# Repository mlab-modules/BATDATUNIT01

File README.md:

# BATDATUNIT01 - Power and Data Storage Module

The BATDATUNIT01 is power and data storage module incorporating an ATmea1284p microcontroller paired with a five 18650 Li-ion safely rechargable accumulator cells. It is a reliable power source for extended durations, making it an integral component in various detectors or measuring systems.

## Features

- **Microcontroller**: [ATmega1284p](https://www.microchip.com/wwwproducts/en/ATmega1284p) provides robust processing capabilities to manage complex tasks efficiently.
- **Battery Pack**: A Set of up to five Li-ion batteries offers substantial power, facilitating long-term operations without frequent recharging.
- **USB-C Charging**: Enables hassle-free charging with a USB-C interface, ensuring the module is readily powered for sustained use.
- **Charging and Monitoring Circuits**: The [BQ25628E](https://www.ti.com/product/BQ25628) circuit oversees the charging, while the [BQ34Z100](https://www.ti.com/product/BQ34Z100) gauge monitors the battery state for optimal energy management.

## Applications

The BATDATUNIT01 is designed for versatility:

- As a **power module for semiconductor particle detectors** like the [AIRDOS04](https://github.com/UniversalScientificTechnologies/AIRDOS04), it ensures uninterrupted data acquisition in environmental monitoring.
- It can be integrated into **remote sensing stations**, providing consistent power and data logging capabilities for long-term ecological studies.
- In **automated weather stations**, the module's resilience and sensor suite offers valuable insights into meteorological conditions.
- The module can be deployed in **mobile robotics** for energy supply and environmental data collection, aiding navigation and decision-making processes.
- It is also ideal for **educational purposes**, as a hands-on tool to teach about energy management, data acquisition, and sensor integration.

The robust design and connectivity options make the BATDATUNIT01 a dependable choice for powering and managing data across many scientific applications.

For more detailed information on interfacing and protocols, please refer to the [ATmea1284p datasheet](https://ww1.microchip.com/downloads/en/DeviceDoc/doc8059.pdf) and the communication standards for [UART](https://en.wikipedia.org/wiki/Universal_asynchronous_receiver-transmitter), [I2C](https://www.i2c-bus.org/), [SPI](https://en.wikipedia.org/wiki/Serial_Peripheral_Interface), and [GPIO](https://en.wikipedia.org/wiki/General-purpose_input/output).

## Design

Designed for convenience, the module allows for fast detachment from the measuring part without tools, streamlining the replacement process. Data can be downloaded during battery charging thanks to onboard memory.

## Schematics

### Internal structure

```mermaid

    flowchart TD

    subgraph a[User interfaceI]
        USB[[USB-C\nData + power]]
        UI1([User interface \n Button + battery indicator])
        UI2([User interface \n Button + 3x LED])
    
    end

    USB --USB --> USW

    FTDI -- I2C --> I2CSW
    FTDI -- UART <--> MCU
    MCU -- I2C --> I2CSW[I2C mux]
    MCU[Microcontroller]
    MCU --SPI <--> SDW
    MCU --> SDW

    subgraph one[Memory interface]
    SDR[SD card] <--> SDI
    SDI[SD card interface] -- USB <--> USW
    USW[USB-SWITCH]
    SDW[SD card \n SPI-SWITCH] <--> SDI
    end

    subgraph three[Digital part ]
    USW -- USB <--> FTDI[FTDI\nI2C + UART]

    I2CSW --I2C--> HYG[Hygrometer]
    I2CSW --I2C--> ALT[Pressure sensor]

    I2CSW -- I2C --> I2Cen

    end

    I2CSW --I2C--> GAUGE
    I2CSW --I2C--> charger

    GAUGE --> UI1
    MCU --> UI2

    GAUGE --> PWR3v3
    GAUGE --> PWR3v3E
    GAUGE --> PWR5vE
    
    USB -- Power --> charger

    subgraph two[POWER sources]
    PWR3v3[Power supply\nfor internal 3.3V]
    PWR3v3E[Power supply\nfor detector 3.3V]
    PWR5vE[Power supply\nfor detector 5V]
    
    charger --> GAUGE[Accumulators gauge]
    GAUGE <==> LIION[(5x Li-ion cells)]
    end
    PWR3v3 --> MCU

    PWR3v3E --> DI
    PWR5vE --> DI

    I2Cen[I2C switch] -- I2C --> DI
    DI[[Detector interface]] == GPIO, SPI <==> MCU

```

## Connectivity

A durable Molex connector brings together data and detection with impressive mechanical resilience. It hosts UART, I2C, SPI buses, and extra GPIO signals, providing extensive interfacing options with various systems. The complementary module to the interface connector is [BATDATSOCKET01](https://github.com/mlab-modules/BATDATSOCKET01).

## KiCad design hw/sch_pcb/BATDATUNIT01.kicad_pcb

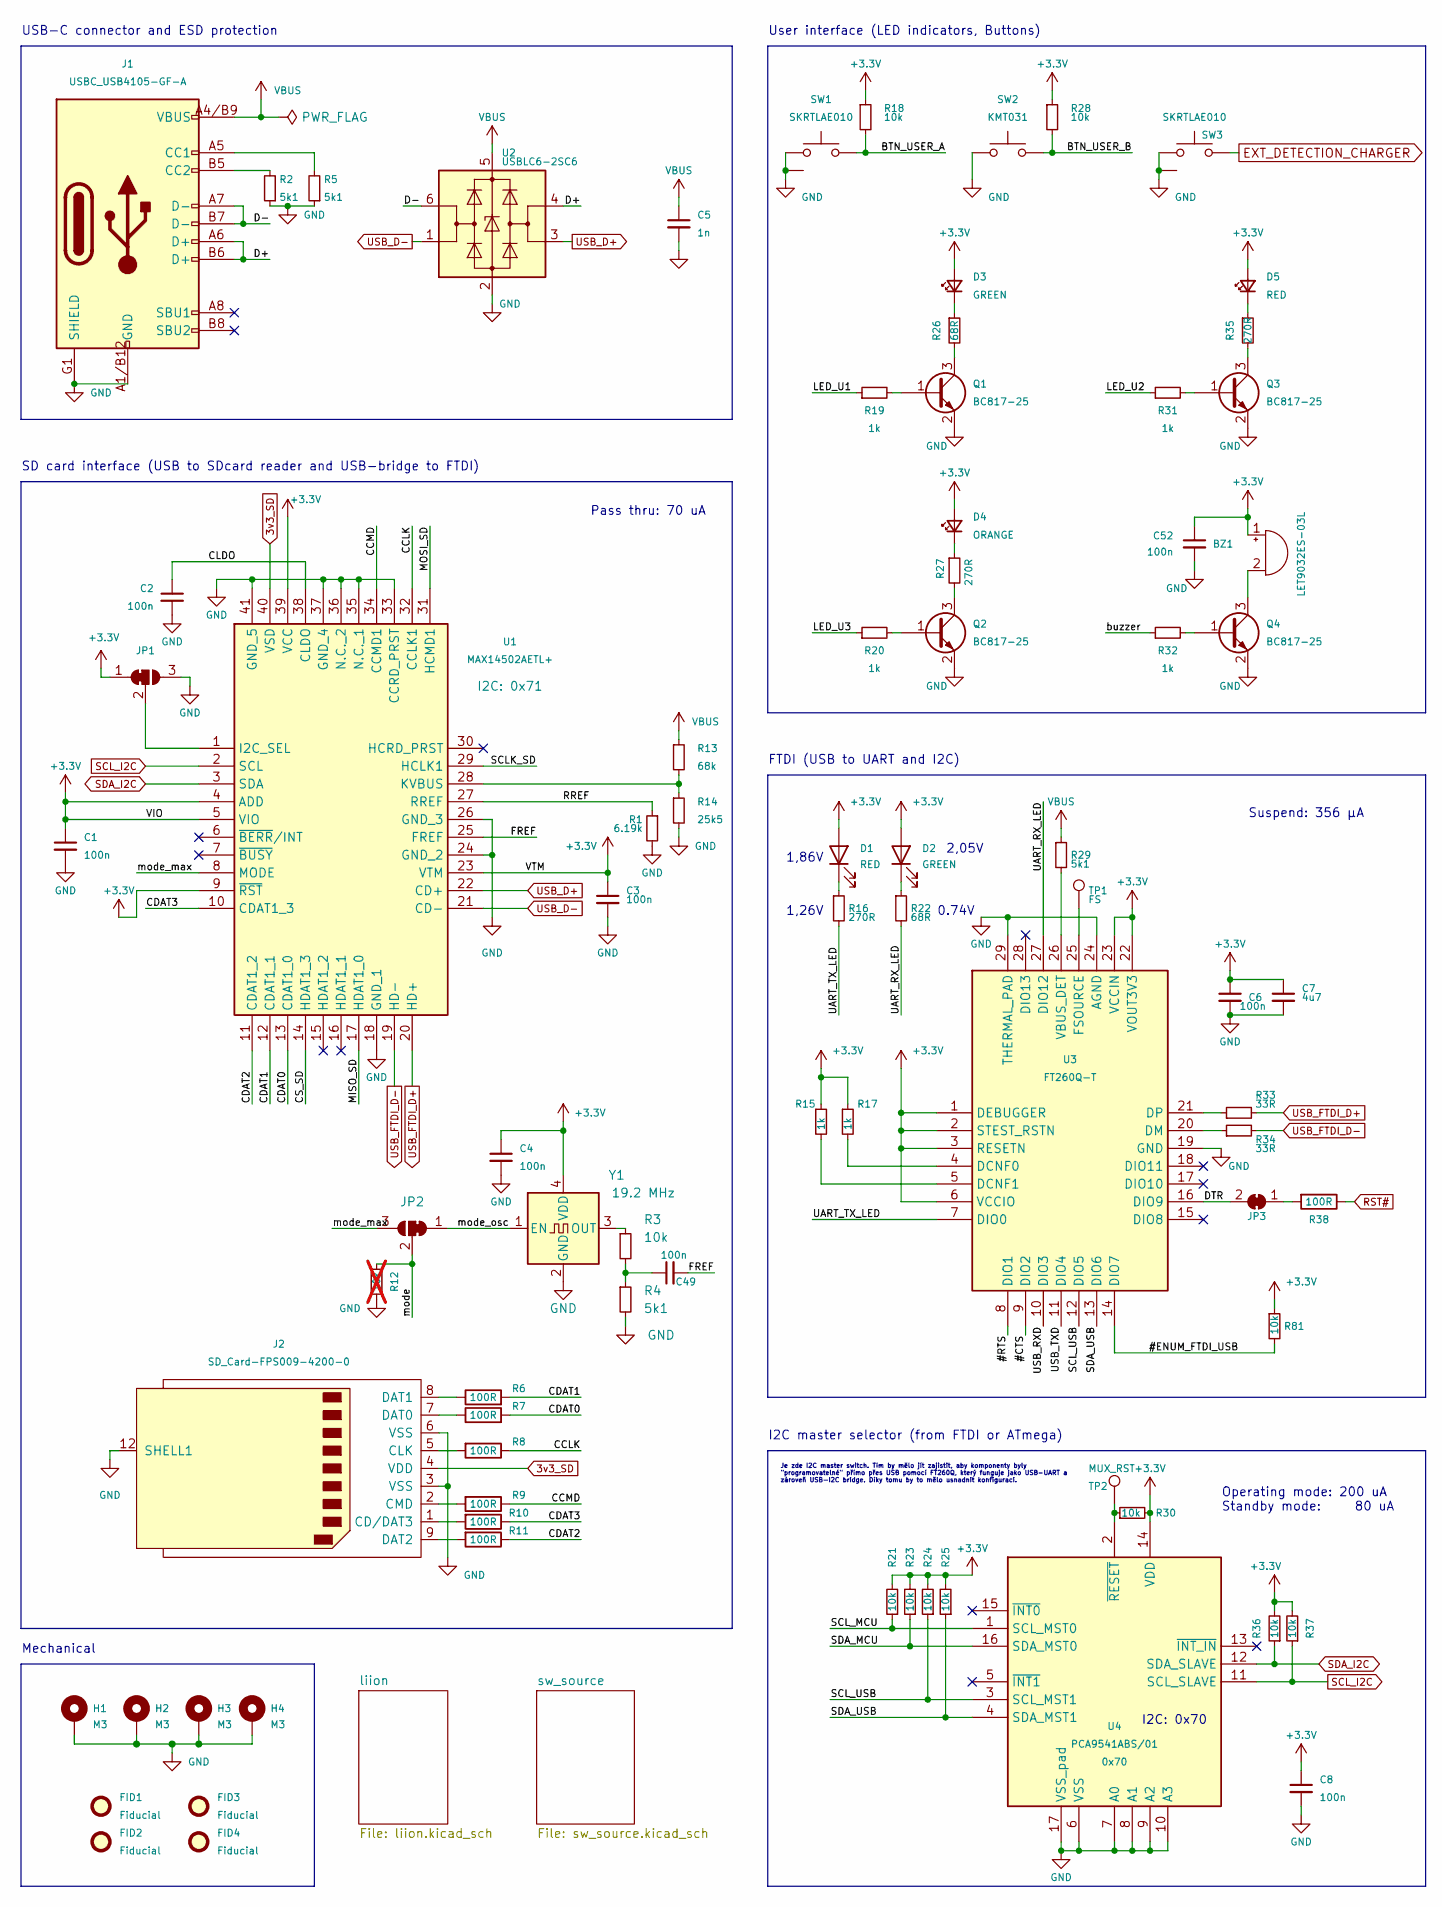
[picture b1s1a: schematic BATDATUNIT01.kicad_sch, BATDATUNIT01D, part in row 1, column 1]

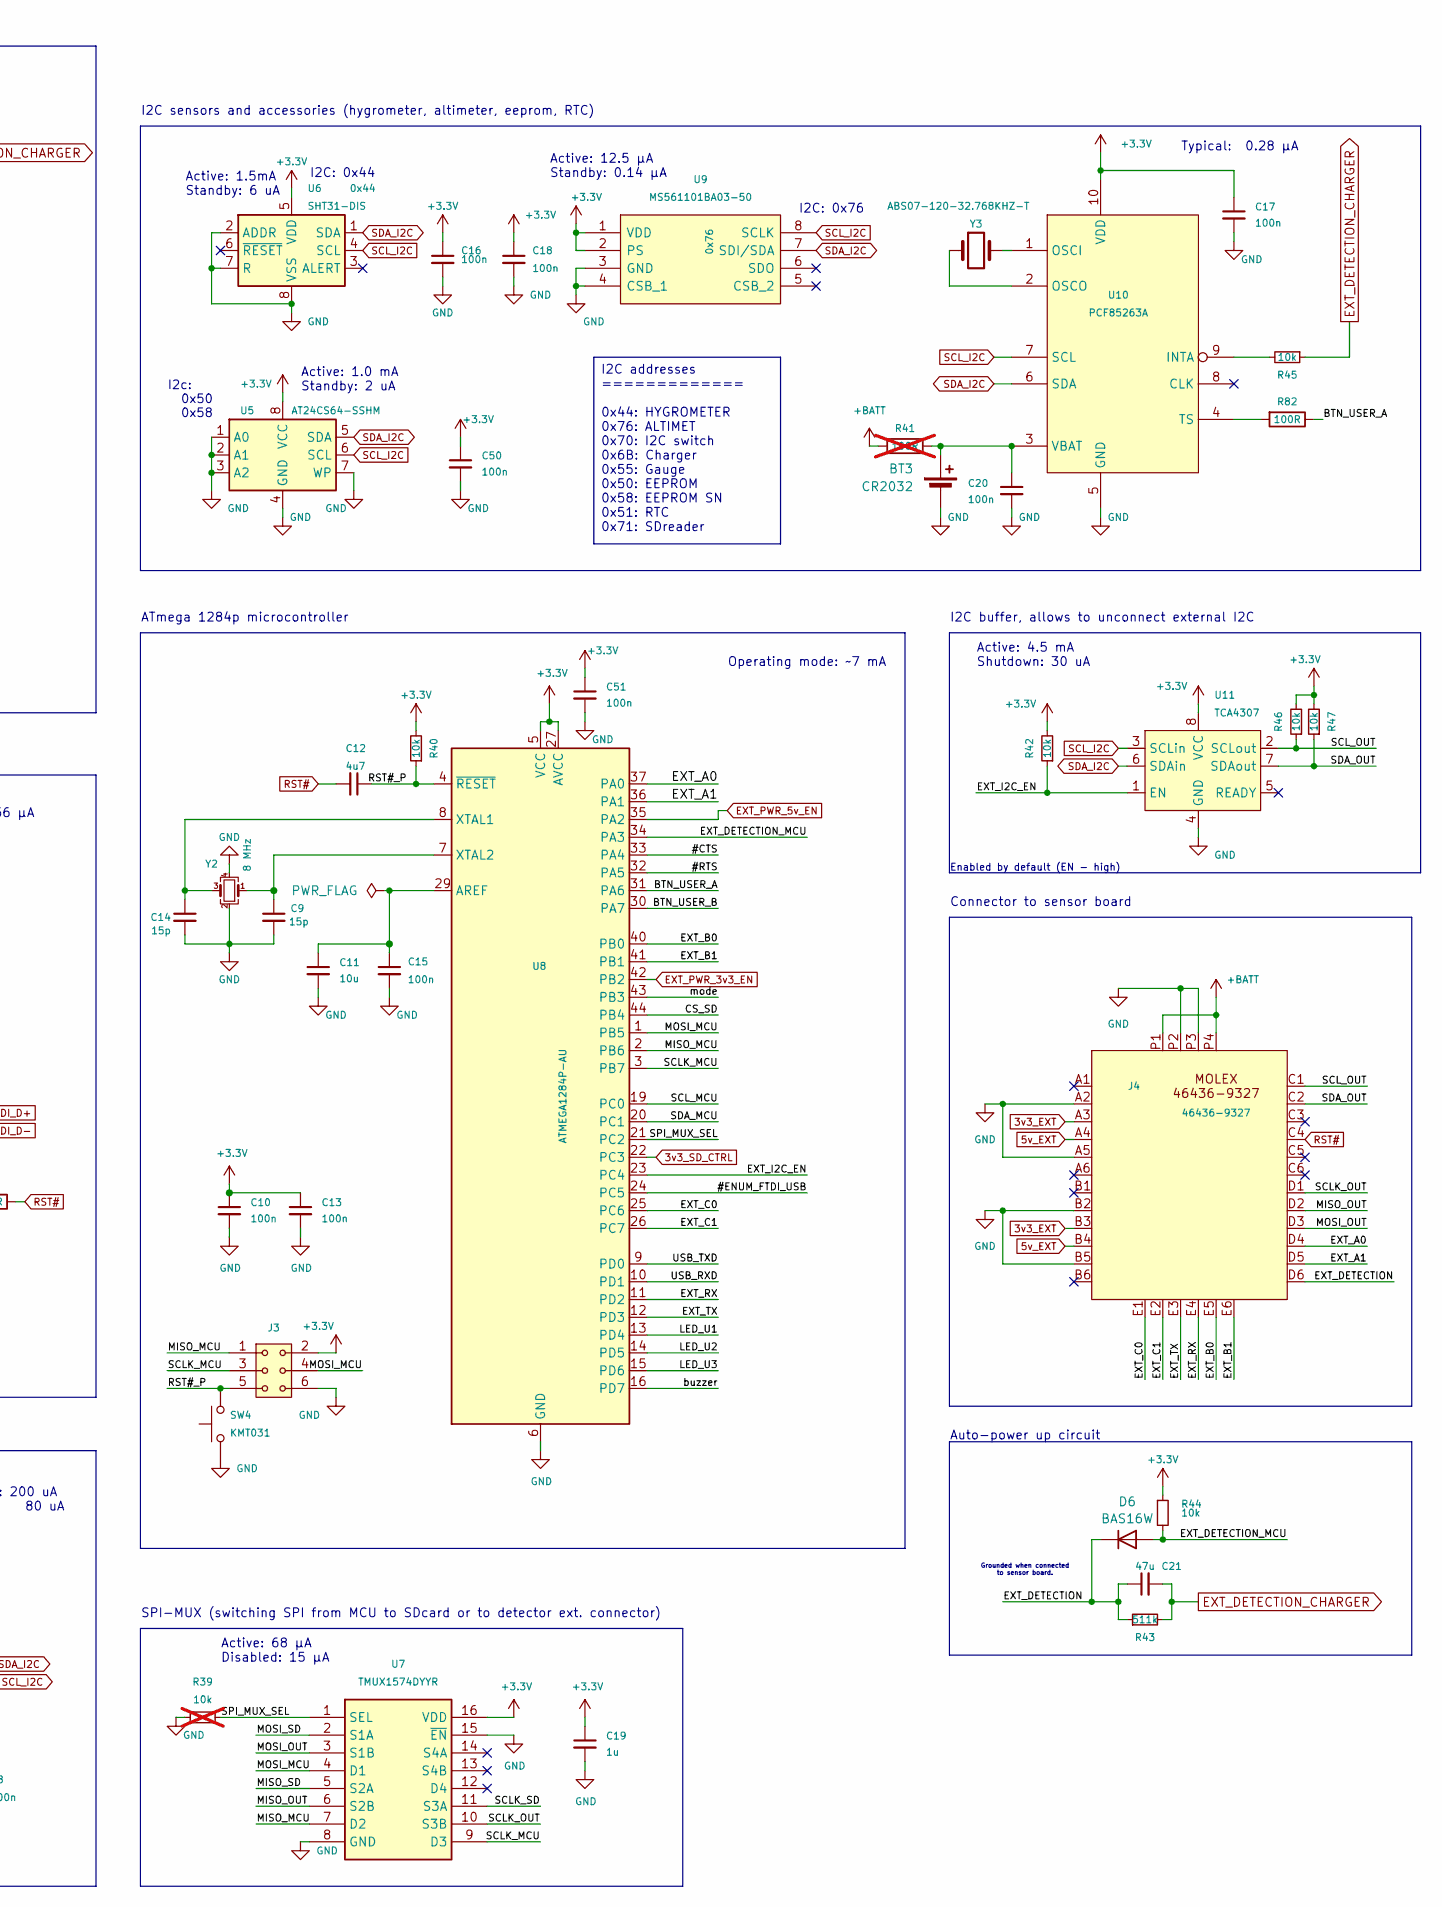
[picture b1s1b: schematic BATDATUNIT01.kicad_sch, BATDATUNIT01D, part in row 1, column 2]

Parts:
BT3: CR2032; BatteryHolder_Keystone_1060_1x2032
BZ1: LET9032ES-03L; MagneticBuzzer_LET9032ES-03L-2.7-16-R
C1, C2, C3, C4, C6, C8, C10, C13, C15, C16, C17, C18, C20, C49, C50, C51, C52: 100n; C_0805_2012Metric
C5: 1n; C_0805_2012Metric; MPN C0805 1u
C7, C12: 4u7; C_0805_2012Metric
C9, C14: 15p; C_0805_2012Metric
C11: 10u; C_0805_2012Metric
C19: 1u; C_0805_2012Metric
C21: 47u; C_0805_2012Metric
D1, D5: RED; SMD_LED_RIGHT_KINGBRIGHT_1605
D2, D3: GREEN; SMD_LED_RIGHT_KINGBRIGHT_1605
D4: ORANGE; SMD_LED_RIGHT_KINGBRIGHT_1605
D6: BAS16W; SOT-323_SC-70
FID1, FID2, FID3, FID4: Fiducial; Fiducial_1mm_Mask2mm
H1, H2, H3, H4: M3; MountingHole_3mm
J1: USBC_USB4105-GF-A; USBC GCT_USB4105-GF-A; MPN USB4105-GF-A
J2: SD_Card-FPS009-4200-0; FPS009-4200-0
J3: HEADER_2x03; SMD_2x03
J4: 46436-9327; MOLEX_46436-9327
JP1: Jumper_3_Bridged12; SolderJumper-3_P1.3mm_Bridged2Bar12_RoundedPad1.0x1.5mm
JP2: SolderJumper_3_Bridged123; SolderJumper-3_P1.3mm_Bridged12_RoundedPad1.0x1.5mm
JP3: SolderJumper_2_Open; SolderJumper-2_P1.3mm_Bridged_RoundedPad1.0x1.5mm
Q1, Q2, Q3, Q4: BC817-25; SOT-23-3
R1: 6.19k; R_0805_2012Metric
R2, R4, R5, R29: 5k1; R_0805_2012Metric
R3, R18, R21, R23, R24, R25, R28, R30, R36, R37, R40, R42, R44, R45, R46, R47, R81: 10k; R_0805_2012Metric
R6, R7, R8, R9, R10, R11, R38, R82: 100R; R_0805_2012Metric
R12, R39: 10k; R_0805_2012Metric; not fitted
R13: 68k; R_0805_2012Metric
R14: 25k5; R_0805_2012Metric
R15, R17, R19, R20, R31, R32: 1k; R_0805_2012Metric
R16, R27, R35: 270R; R_0805_2012Metric
R22, R26: 68R; R_0805_2012Metric
R33, R34: 33R; R_0805_2012Metric
R41: 100R; R_0805_2012Metric; not fitted
R43: 511k; R_0805_2012Metric
SW1, SW3: SKRTLAE010; SKRT
SW2, SW4: KMT031; KMT031 NGJ LHS C&K
TP1: FS; TestPoint_Pad_D1.0mm
TP2: MUX_RST; TestPoint_Pad_D1.5mm
U1: MAX14502AETL+; QFN40P500X500X80-41N; Manufacturer_Part_Number MAX14502AETL+
U2: USBLC6-2SC6; SOT-23-6; LCSC C7519
U3: FT260Q-T; QFN-28-1EP_5x5mm_P0.5mm_EP3.35x3.35mm; Manufacturer_Part_Number FT260Q-T; Mouser Part Number 895-FT260Q-T
U4: PCA9541ABS/01; QFN-16-1EP_4x4mm_P0.65mm_EP2.15x2.15mm; Manufacturer_Part_Number PCA9541ABS/03,118; Mouser Part Number 771-PCA9541ABS03,118
U5: AT24CS64-SSHM; SOIC-8_3.9x4.9mm_P1.27mm
U6: SHT31-DIS; Sensirion_DFN-8-1EP_2.5x2.5mm_P0.5mm_EP1.1x1.7mm
U7: TMUX1574DYYR; SOT-23-16 THIN; Manufacturer_Part_Number TMUX1574DYYR; Mouser Part Number 595-TMUX1574DYYR
U8: ATMEGA1284P-AU; TQFP-44_10x10mm_P0.8mm
U9: MS561101BA03-50; LGA-8_3x5mm_P1.25mm; Mouser Part Number 824-MS561101BA03-50
U10: PCF85263A; TSSOP-10_3x3mm_P0.5mm
U11: TCA4307; VSSOP-8_3.0x3.0mm_P0.65mm
Y1: 19.2 MHz; Crystal_SMD_2520-4Pin_2.5x2.0mm
Y2: 8 MHz; Crystal_SMD_3225-4Pin_3.2x2.5mm
Y3: ABS07-120-32.768KHZ-T; ABS07

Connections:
3v3_EXT: J4.A3, J4.B3; also elsewhere on the board
3v3_SD: J2.4 (VDD), U1.40 (VSD); also elsewhere on the board
3v3_SD_CTRL: U8.22 (PC3); also elsewhere on the board
5v_EXT: J4.A4, J4.B4; also elsewhere on the board
+3.3V: BZ1.1 (-), C1.1, C3.1, C4.1, C6.1, C7.1, C8.1, C10.1, C13.1, C16.1, C17.1, C18.1, C19.1, C50.1, C51.1, C52.1, D1.2 (A), D2.2 (A), D3.2 (A), D4.2 (A), D5.2 (A), J3.2, JP1.1 (A), R15.1, R17.1, R18.1, R21.2, R23.2, R24.2, R25.2, R28.1, R30.2, R36.2, R37.2, R40.2, R42.2, R44.1, R46.2, R47.2, R81.1, U1.4 (ADD), U1.5 (VIO), U1.9 (~RST), U1.23 (VTM), U1.39 (VCC), U3.1 (DEBUGGER), U3.2 (STEST_RSTN), U3.3 (RESETN), U3.6 (VCCIO), U3.22 (VOUT3V3), U3.23 (VCCIN), U4.14 (VDD), U5.8 (VCC), U6.5 (VDD), U7.16 (VDD), U8.5 (VCC), U8.17 (VCC), U8.27 (AVCC), U8.38 (VCC), U9.1 (VDD), U9.2 (PS), U10.10 (VDD), U11.8 (VCC), Y1.4 (VDD); also elsewhere on the board
+BATT: J4.P1, J4.P4, R41.2; also elsewhere on the board
/#CTS: U3.9 (DIO2), U8.33 (PA4)
/#ENUM_FTDI_USB: R81.2, U3.14 (DIO7), U8.24 (PC5)
/#RTS: U3.8 (DIO1), U8.32 (PA5)
/BTN_USER_A: R18.2, R82.1, SW1.1, U8.31 (PA6)
/BTN_USER_B: R28.2, SW2.1, U8.30 (PA7)
/CCLK: R8.1, U1.32 (CCLK1)
/CCMD: R9.1, U1.34 (CCMD1)
/CDAT0: R7.2, U1.13 (CDAT1_0)
/CDAT1: R6.2, U1.12 (CDAT1_1)
/CDAT2: R11.1, U1.11 (CDAT1_2)
/CDAT3: R10.1, U1.10 (CDAT1_3)
/CLDO: C2.1, U1.38 (CLDO)
/CS_SD: U1.14 (HDAT1_3), U8.44 (PB4)
/D+: J1.A6 (D+), J1.B6 (D+), U2.4 (I/O2)
/D-: J1.A7 (D-), J1.B7 (D-), U2.6 (I/O1)
/DTR: JP3.2 (B), U3.16 (DIO9)
/EXT_A0: J4.D4, U8.37 (PA0)
/EXT_A1: J4.D5, U8.36 (PA1)
/EXT_B0: J4.E5, U8.40 (PB0)
/EXT_B1: J4.E6, U8.41 (PB1)
/EXT_C0: J4.E1, U8.25 (PC6)
/EXT_C1: J4.E2, U8.26 (PC7)
/EXT_DETECTION: C21.1, D6.3 (K), J4.D6, R43.1
/EXT_DETECTION_MCU: D6.1 (A), R44.2, U8.34 (PA3)
/EXT_I2C_EN: R42.1, U8.23 (PC4), U11.1 (EN)
/EXT_RX: J4.E4, U8.11 (PD2)
/EXT_TX: J4.E3, U8.12 (PD3)
/FREF: C49.2, U1.25 (FREF)
/LED_U1: R19.1, U8.13 (PD4)
/LED_U2: R31.1, U8.14 (PD5)
/LED_U3: R20.1, U8.15 (PD6)
/MISO_MCU: J3.1, U7.7 (D2), U8.2 (PB6)
/MISO_OUT: J4.D2, U7.6 (S2B)
/MISO_SD: U1.17 (HDAT1_0), U7.5 (S2A)
/MOSI_MCU: J3.4, U7.4 (D1), U8.1 (PB5)
/MOSI_OUT: J4.D3, U7.3 (S1B)
/MOSI_SD: U1.31 (HCMD1), U7.2 (S1A)
/RREF: R1.1, U1.27 (RREF)
/RST#_P: C12.1, J3.5, R40.1, SW4.2, U8.4 (~RESET)
/SCLK_MCU: J3.3, U7.9 (D3), U8.3 (PB7)
/SCLK_OUT: J4.D1, U7.10 (S3B)
/SCLK_SD: U1.29 (HCLK1), U7.11 (S3A)
/SCL_MCU: R21.1, U4.1 (SCL_MST0), U8.19 (PC0)
/SCL_OUT: J4.C1, R46.1, U11.2 (SCLout)
/SCL_USB: R24.1, U3.12 (DIO5), U4.3 (SCL_MST1)
/SDA_MCU: R23.1, U4.16 (SDA_MST0), U8.20 (PC1)
/SDA_OUT: J4.C2, R47.1, U11.7 (SDAout)
/SDA_USB: R25.1, U3.13 (DIO6), U4.4 (SDA_MST1)
/SPI_MUX_SEL: R39.2, U7.1 (SEL), U8.21 (PC2)
/UART_RX_LED: R22.2, U3.27 (DIO12)
/UART_TX_LED: R16.2, U3.7 (DIO0)
/USB_RXD: U3.10 (DIO3), U8.10 (PD1)
/USB_TXD: U3.11 (DIO4), U8.9 (PD0)
/buzzer: R32.1, U8.16 (PD7)
/mode: JP2.2 (C), R12.2, U8.43 (PB3)
/mode_max: JP2.3 (B), U1.8 (MODE)
/mode_osc: JP2.1 (A), Y1.1 (EN)
EXT_DETECTION_CHARGER: C21.2, R43.2, R45.1, SW3.1; also elsewhere on the board
EXT_PWR_3v3_EN: U8.42 (PB2); also elsewhere on the board
EXT_PWR_5v_EN: U8.35 (PA2); also elsewhere on the board
GND: BT3.2 (-), C1.2, C2.2, C3.2, C4.2, C5.2, C6.2, C7.2, C8.2, C9.2, C10.2, C11.2, C13.2, C14.2, C15.2, C16.2, C17.2, C18.2, C19.2, C20.2, C50.2, C51.2, C52.2, H1.1 (1_1), H2.1 (1_1), H3.1 (1_1), H4.1 (1_1), J1.A1/B12 (GND), J1.B1/A12 (GND), J1.G1 (SHIELD), J1.G2 (SHIELD), J1.G3 (SHIELD), J1.G4 (SHIELD), J2.3 (VSS), J2.6 (VSS), J2.12 (SHELL1), J3.6, J4.A2, J4.A5, J4.B2, J4.B5, J4.P2, J4.P3, JP1.3 (B), Q1.2 (E), Q2.2 (E), Q3.2 (E), Q4.2 (E), R1.2, R2.1, R4.2, R5.1, R12.1, R14.2, R39.1, SW1.2, SW1.GND (SHIELD), SW2.2, SW3.2, SW3.GND (SHIELD), SW4.1, U1.18 (GND_1), U1.24 (GND_2), U1.26 (GND_3), U1.33 (CCRD_PRST), U1.35 (N.C._1), U1.36 (N.C._2), U1.37 (GND_4), U1.41 (GND_5), U2.2 (GND), U3.19 (GND), U3.24 (AGND), U3.29 (THERMAL_PAD), U4.6 (VSS), U4.7 (A0), U4.8 (A1), U4.9 (A2), U4.10 (A3), U4.17 (VSS_pad), U5.1 (A0), U5.2 (A1), U5.3 (A2), U5.4 (GND), U5.7 (WP), U6.2 (ADDR), U6.7 (R), U6.8 (VSS), U6.9 (VSS), U7.8 (GND), U7.15 (~EN), U8.6 (GND), U8.18 (GND), U8.28 (GND), U8.39 (GND), U9.3 (GND), U9.4 (CSB_1), U10.5 (GND), U11.4 (GND), Y1.2 (GND), Y2.2, Y2.4; also elsewhere on the board
unnamed: BT3.1 (+), C20.1, R41.1, U10.3 (VBAT)
unnamed: BZ1.2 (+), Q4.3 (C)
unnamed: C49.1, R3.2, R4.1
unnamed: D1.1 (K), R16.1
unnamed: D2.1 (K), R22.1
unnamed: D3.1 (K), R26.1
unnamed: D4.1 (K), R27.1
unnamed: D5.1 (K), R35.1
unnamed: J1.A5 (CC1), R5.2
unnamed: J1.B5 (CC2), R2.2
unnamed: J2.1 (CD/DAT3), R10.2
unnamed: J2.5 (CLK), R8.2
unnamed: J2.2 (CMD), R9.2
unnamed: J2.7 (DAT0), R7.1
unnamed: J2.8 (DAT1), R6.1
unnamed: J2.9 (DAT2), R11.2
unnamed: JP1.2 (C), U1.1 (I2C_SEL)
unnamed: JP3.1 (A), R38.2
unnamed: Q1.1 (B), R19.2
unnamed: Q1.3 (C), R26.2
unnamed: Q2.1 (B), R20.2
unnamed: Q2.3 (C), R27.2
unnamed: Q3.1 (B), R31.2
unnamed: Q3.3 (C), R35.2
unnamed: Q4.1 (B), R32.2
unnamed: R13.2, R14.1, U1.28 (KVBUS)
unnamed: R17.2, U3.4 (DCNF0)
unnamed: R15.2, U3.5 (DCNF1)
unnamed: R34.1, U3.20 (DM)
unnamed: R33.1, U3.21 (DP)
unnamed: TP1.1 (1_1), U3.25 (FSOURCE)
unnamed: R29.2, U3.26 (VBUS_DET)
unnamed: R30.1, TP2.1 (1_1), U4.2 (~RESET)
unnamed: C11.1, C15.1, U8.29 (AREF)
unnamed: C14.1, U8.8 (XTAL1), Y2.3
unnamed: C9.1, U8.7 (XTAL2), Y2.1
unnamed: R45.2, U10.9 (INTA)
unnamed: U10.1 (OSCI), Y3.2
unnamed: U10.2 (OSCO), Y3.1
unnamed: R82.2, U10.4 (TS)
unnamed: R3.1, Y1.3 (OUT)
RST#: C12.2, J4.C4, R38.1
SCL_I2C: R37.1, U1.2 (SCL), U4.11 (SCL_SLAVE), U5.6 (SCL), U6.4 (SCL), U9.8 (SCLK), U10.7 (SCL), U11.3 (SCLin); also elsewhere on the board
SDA_I2C: R36.1, U1.3 (SDA), U4.12 (SDA_SLAVE), U5.5 (SDA), U6.1 (SDA), U9.7 (SDI/SDA), U10.6 (SDA), U11.6 (SDAin); also elsewhere on the board
USB_D+: U1.22 (CD+), U2.3 (I/O2)
USB_D-: U1.21 (CD-), U2.1 (I/O1)
USB_FTDI_D+: R33.2, U1.20 (HD+)
USB_FTDI_D-: R34.2, U1.19 (HD-)
VBUS: C5.1, J1.A4/B9 (VBUS), J1.B4/A9 (VBUS), R13.1, R29.1, U2.5 (VBUS); also elsewhere on the board

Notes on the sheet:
SPI-MUX (switching SPI from MCU to SDcard or to detector ext. connector)
Active: 4.5 mA Shutdown: 30 uA
Active: 1.5mA Standby: 6 uA
0.74V
Active: 1.0 mA Standby: 2 uA
Suspend: 356 μA
FTDI (USB to UART and I2C)
I2C: 0x44
Active: 12.5 μA Standby: 0.14 μA
Mechanical
I2C buffer, allows to unconnect external I2C
ATmega 1284p microcontroller
1,86V
Pass thru: 70 uA
USB-C connector and ESD protection
Typical: 0.28 μA
I2C sensors and accessories (hygrometer, altimeter, eeprom, RTC)
I2C master selector (from FTDI or ATmega)
User interface (LED indicators, Buttons)
Operating mode: ~7 mA
Auto-power up circuit
Active: 68 μA Disabled: 15 μA
Grounded when connected to sensor board.
2,05V
Connector to sensor board
I2c: 0x50 0x58
I2C: 0x76
Enabled by default (EN - high)
I2C: 0x70
1,26V
Operating mode: 200 uA Standby mode: 80 uA
SD card interface (USB to SDcard reader and USB-bridge to FTDI)
I2C addresses ============= 0x44: HYGROMETER 0x76: ALTIMET 0x70: I2C switch 0x6B: Charger 0x55: Gauge 0x50: EEPROM 0x58: EEPROM SN 0x51: RTC 0x71: SDreader
Je zde I2C master switch. Tím by mělo jít zajistit, aby komponenty byly "programovatelné" přímo přes USB pomocí FT260Q, který funguje jako USB-UART a zároveň USB-I2C bridge. Díky tomu by to mělo usnadnit konfiguraci.

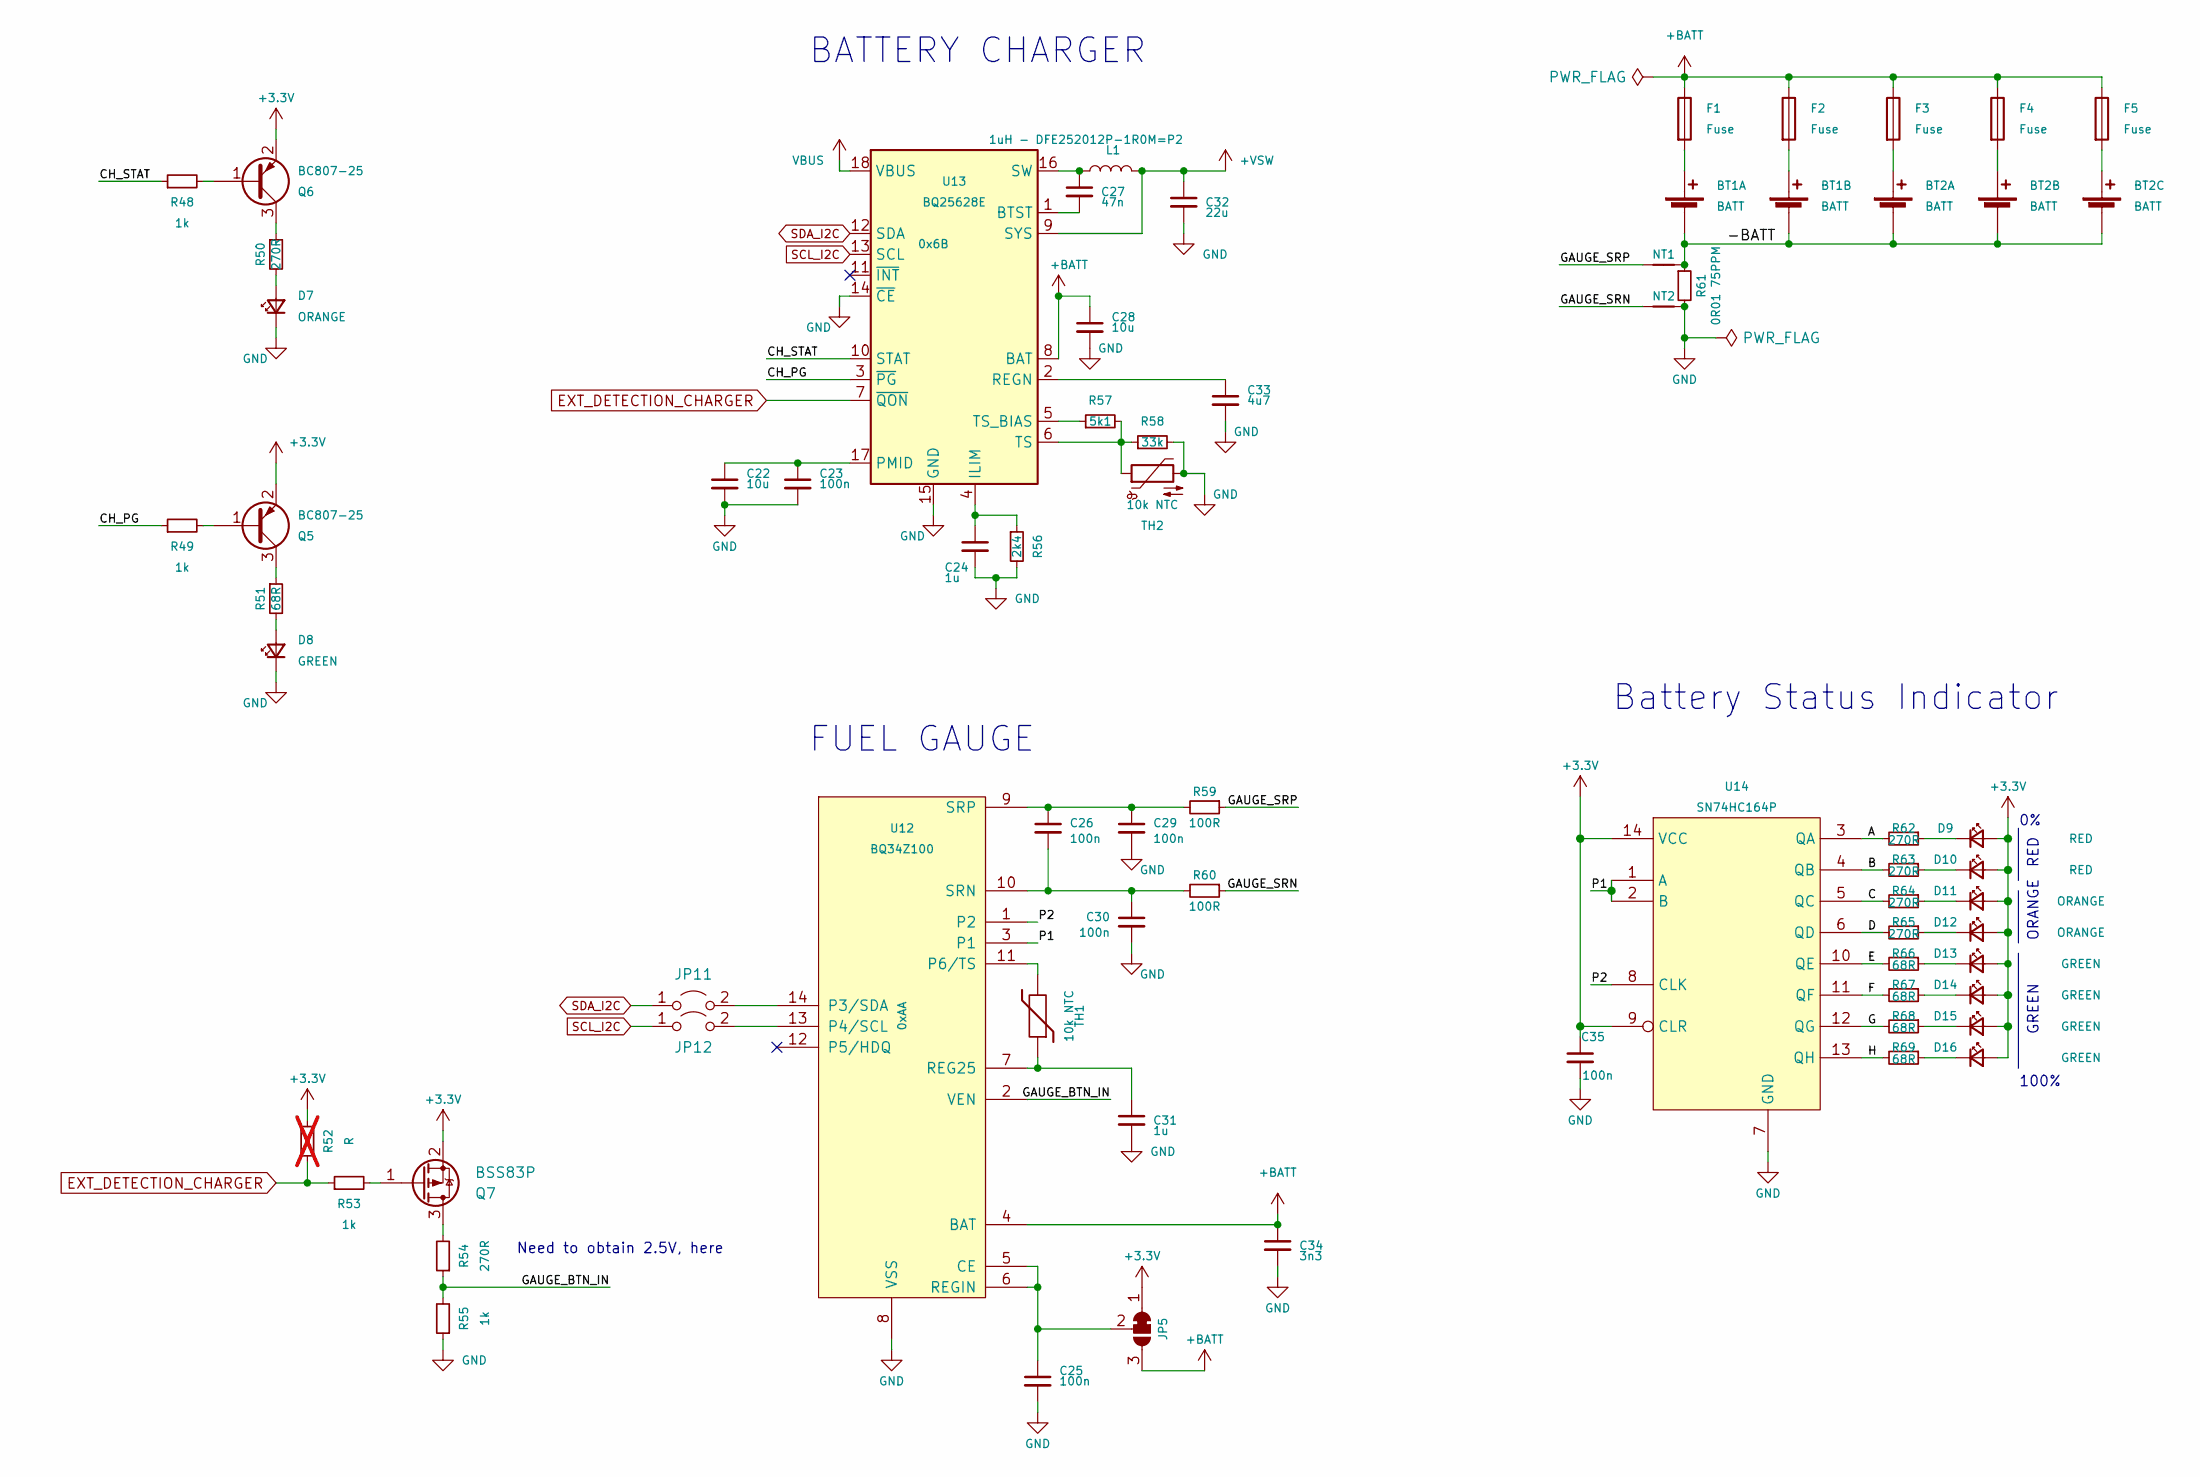
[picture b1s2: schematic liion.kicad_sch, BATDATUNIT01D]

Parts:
BT1: BATT; BAT_BK-18650-PC4
BT2: BATT; BAT_BK-18650-PC6
C22, C28: 10u; C_0805_2012Metric
C23, C25, C26, C29, C30, C35: 100n; C_0805_2012Metric
C24, C31: 1u; C_0805_2012Metric
C27: 47n; C_0805_2012Metric
C32: 22u; C_0805_2012Metric
C33: 4u7; C_0805_2012Metric
C34: 3n3; C_0805_2012Metric
D7, D11, D12: ORANGE; SMD_LED_RIGHT_KINGBRIGHT_1605
D8, D13, D14, D15, D16: GREEN; SMD_LED_RIGHT_KINGBRIGHT_1605
D9, D10: RED; SMD_LED_RIGHT_KINGBRIGHT_1605
F1, F2, F3, F4, F5: Fuse; Fuseholder_Littelfuse_Nano2_154x
JP5: Jumper_3_Bridged12; SolderJumper-3_P1.3mm_Bridged2Bar12_RoundedPad1.0x1.5mm
JP11, JP12: Jumper_2_Open; SolderJumper-2_P1.3mm_Open_RoundedPad1.0x1.5mm
L1: 1uH - DFE252012P-1R0M=P2; L_1008_2520Metric
NT1, NT2: NetTie_2; NetTie-2_SMD_Pad0.5mm
Q5, Q6: BC807-25; SOT-23-3
Q7: BSS83P; SOT-23
R48, R49, R53, R55: 1k; R_0805_2012Metric
R50, R54, R62, R63, R64, R65: 270R; R_0805_2012Metric
R51, R66, R67, R68, R69: 68R; R_0805_2012Metric
R52: R; R_0805_2012Metric; not fitted
R56: 2k4; R_0805_2012Metric
R57: 5k1; R_0805_2012Metric
R58: 33k; R_0805_2012Metric
R59, R60: 100R; R_0805_2012Metric
R61: 0R01 75PPM; R_2512_6332Metric
TH1, TH2: 10k NTC; R_0805_2012Metric
U12: BQ34Z100; TSSOP-14_4.4x5mm_Pitch0.65mm
U13: BQ25628E; Texas_S-WQFN-HR-18
U14: SN74HC164P; TSSOP-14_4.4x5mm_P0.65mm

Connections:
+3.3V: C35.1, D9.2 (A), D10.2 (A), D11.2 (A), D12.2 (A), D13.2 (A), D14.2 (A), D15.2 (A), D16.2 (A), JP5.1 (A), Q5.2 (E), Q6.2 (E), Q7.2 (S), R52.2, U14.9 (CLR), U14.14 (VCC); also elsewhere on the board
+BATT: C28.1, C34.1, F1.1, F2.1, F3.1, F4.1, F5.1, JP5.3 (B), U12.4 (BAT), U13.8 (BAT); also elsewhere on the board
+VSW: C32.1, L1.2, U13.9 (SYS); also elsewhere on the board
/liion/-BATT: BT1.1- (-), BT1.2- (-), BT2.1- (-), BT2.2- (-), BT2.3- (-), NT1.2, R61.1
/liion/A: R62.2, U14.3 (QA)
/liion/B: R63.2, U14.4 (QB)
/liion/C: R64.2, U14.5 (QC)
/liion/CH_PG: R49.1, U13.3 (~PG)
/liion/CH_STAT: R48.1, U13.10 (STAT)
/liion/D: R65.2, U14.6 (QD)
/liion/E: R66.2, U14.10 (QE)
/liion/F: R67.2, U14.11 (QF)
/liion/G: R68.2, U14.12 (QG)
/liion/GAUGE_BTN_IN: R54.1, R55.2, U12.2 (VEN)
/liion/GAUGE_SRN: NT2.1, R60.1
/liion/GAUGE_SRP: NT1.1, R59.1
/liion/H: R69.2, U14.13 (QH)
/liion/P1: U12.3 (P1), U14.1 (A), U14.2 (B)
/liion/P2: U12.1 (P2), U14.8 (CLK)
EXT_DETECTION_CHARGER: R52.1, R53.1, U13.7 (~QON); also elsewhere on the board
GND: C22.2, C23.2, C24.2, C25.2, C28.2, C29.2, C30.2, C31.2, C32.2, C33.2, C34.2, C35.2, D7.1 (K), D8.1 (K), NT2.2, R55.1, R56.2, R58.2, R61.2, TH2.2, U12.8 (VSS), U13.14 (~CE), U13.15 (GND), U14.7 (GND); also elsewhere on the board
unnamed: BT1.1+ (+), F1.2
unnamed: BT1.2+ (+), F2.2
unnamed: BT2.1+ (+), F3.2
unnamed: BT2.2+ (+), F4.2
unnamed: BT2.3+ (+), F5.2
unnamed: D7.2 (A), R50.2
unnamed: D8.2 (A), R51.2
unnamed: D9.1 (K), R62.1
unnamed: D10.1 (K), R63.1
unnamed: D11.1 (K), R64.1
unnamed: D12.1 (K), R65.1
unnamed: D13.1 (K), R66.1
unnamed: D14.1 (K), R67.1
unnamed: D15.1 (K), R68.1
unnamed: D16.1 (K), R69.1
unnamed: C25.1, JP5.2 (C), U12.5 (CE), U12.6 (REGIN)
unnamed: JP11.2 (B), U12.14 (P3/SDA)
unnamed: JP12.2 (B), U12.13 (P4/SCL)
unnamed: Q5.1 (B), R49.2
unnamed: Q5.3 (C), R51.1
unnamed: Q6.1 (B), R48.2
unnamed: Q6.3 (C), R50.1
unnamed: Q7.3 (D), R54.2
unnamed: Q7.1 (G), R53.2
unnamed: TH1.2, U12.11 (P6/TS)
unnamed: C31.1, TH1.1, U12.7 (REG25)
unnamed: C26.2, C30.1, R60.2, U12.10 (SRN)
unnamed: C26.1, C29.1, R59.2, U12.9 (SRP)
unnamed: C27.2, U13.1 (BTST)
unnamed: C24.1, R56.1, U13.4 (ILIM)
unnamed: C22.1, C23.1, U13.17 (PMID)
unnamed: C33.1, U13.2 (REGN)
unnamed: C27.1, L1.1, U13.16 (SW)
unnamed: R57.2, R58.1, TH2.1, U13.6 (TS)
unnamed: R57.1, U13.5 (TS_BIAS)
SCL_I2C: JP12.1 (A), U13.13 (SCL); also elsewhere on the board
SDA_I2C: JP11.1 (A), U13.12 (SDA); also elsewhere on the board
VBUS: U13.18 (VBUS); also elsewhere on the board

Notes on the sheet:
Need to obtain 2.5V, here
GREEN
FUEL GAUGE
100%
RED
Battery Status Indicator
ORANGE
BATTERY CHARGER
